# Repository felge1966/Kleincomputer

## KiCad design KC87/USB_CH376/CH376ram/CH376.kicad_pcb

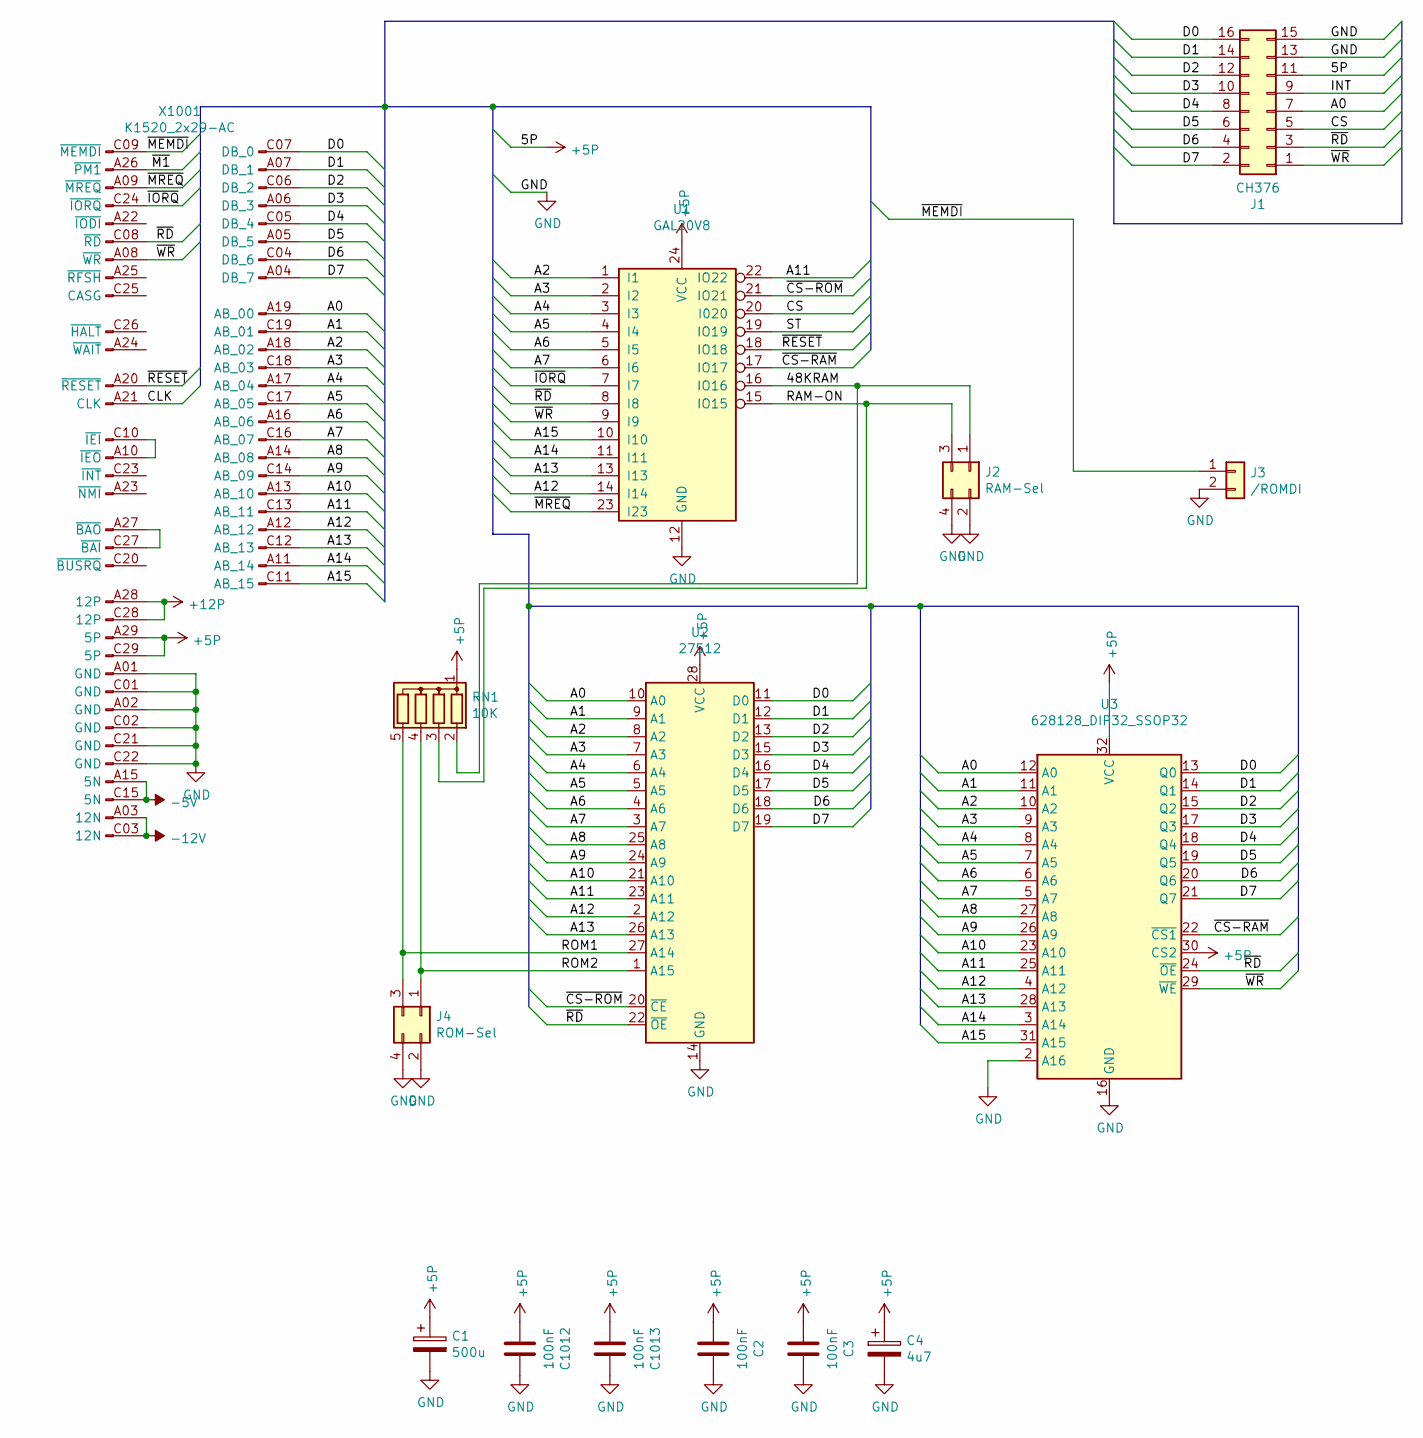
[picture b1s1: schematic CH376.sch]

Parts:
C1: 500u; CP_Radial_D8.0mm_P2.50mm
C2, C3, C1012, C1013: 100nF; C_Disc_D3.0mm_W2.0mm_P2.50mm
C4: 4u7; CP_Radial_D5.0mm_P2.50mm
J1: CH376; PinSocket_2x08_P2.54mm_Vertical
J2: RAM-Sel; PinHeader_2x02_P2.54mm_Horizontal
J3: /ROMDI; PinHeader_1x02_P2.54mm_Horizontal
J4: ROM-Sel; PinHeader_2x02_P2.54mm_Horizontal
RN1: 10K; R_Array_SIP5
U1: GAL20V8; DIP-24_W7.62mm_LongPads
U2: 27512; DIP-28_W15.24mm
U3: 628128_DIP32_SSOP32; DIP-32_W15.24mm_LongPads
X1001: K1520_2x29-AC; K1520_EFS2x29_DIN_male

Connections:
+5P: C1.1, C2.2, C3.2, C4.1, C1012.2, C1013.2, J1.11, RN1.1 (common), U1.24 (VCC), U2.28 (VCC), U3.30 (CS2), U3.32 (VCC), X1001.A29 (5P), X1001.C29 (5P)
+12P: X1001.A28 (12P), X1001.C28 (12P)
-5V: X1001.A15 (5N), X1001.C15 (5N)
-12V: X1001.A03 (12N), X1001.C03 (12N)
/48KRAM: J2.1, RN1.2 (R1), U1.16 (IO16)
/A0: J1.7, U2.10 (A0), U3.12 (A0), X1001.A19 (AB_00)
/A1: U2.9 (A1), U3.11 (A1), X1001.C19 (AB_01)
/A2: U1.1 (I1), U2.8 (A2), U3.10 (A2), X1001.A18 (AB_02)
/A3: U1.2 (I2), U2.7 (A3), U3.9 (A3), X1001.C18 (AB_03)
/A4: U1.3 (I3), U2.6 (A4), U3.8 (A4), X1001.A17 (AB_04)
/A5: U1.4 (I4), U2.5 (A5), U3.7 (A5), X1001.C17 (AB_05)
/A6: U1.5 (I5), U2.4 (A6), U3.6 (A6), X1001.A16 (AB_06)
/A7: U1.6 (I6), U2.3 (A7), U3.5 (A7), X1001.C16 (AB_07)
/A8: U2.25 (A8), U3.27 (A8), X1001.A14 (AB_08)
/A9: U2.24 (A9), U3.26 (A9), X1001.C14 (AB_09)
/A10: U2.21 (A10), U3.23 (A10), X1001.A13 (AB_10)
/A11: U1.22 (IO22), U2.23 (A11), U3.25 (A11), X1001.C13 (AB_11)
/A12: U1.14 (I14), U2.2 (A12), U3.4 (A12), X1001.A12 (AB_12)
/A13: U1.13 (I13), U2.26 (A13), U3.28 (A13), X1001.C12 (AB_13)
/A14: U1.11 (I11), U3.3 (A14), X1001.A11 (AB_14)
/A15: U1.10 (I10), U3.31 (A15), X1001.C11 (AB_15)
/CLK: X1001.A21 (CLK)
/CS: J1.5, U1.20 (I020)
/D0: J1.16, U2.11 (D0), U3.13 (Q0), X1001.C07 (DB_0)
/D1: J1.14, U2.12 (D1), U3.14 (Q1), X1001.A07 (DB_1)
/D2: J1.12, U2.13 (D2), U3.15 (Q2), X1001.C06 (DB_2)
/D3: J1.10, U2.15 (D3), U3.17 (Q3), X1001.A06 (DB_3)
/D4: J1.8, U2.16 (D4), U3.18 (Q4), X1001.C05 (DB_4)
/D5: J1.6, U2.17 (D5), U3.19 (Q5), X1001.A05 (DB_5)
/D6: J1.4, U2.18 (D6), U3.20 (Q6), X1001.C04 (DB_6)
/D7: J1.2, U2.19 (D7), U3.21 (Q7), X1001.A04 (DB_7)
/RAM-ON: J2.3, RN1.3 (R2), U1.15 (IO15)
/ROM1: J4.3, RN1.5 (R4), U2.27 (A14)
/ROM2: J4.1, RN1.4 (R3), U2.1 (A15)
/~CS-RAM: U1.17 (IO17), U3.22 (~CS1)
/~CS-ROM: U1.21 (IO21), U2.20 (~CE)
/~IORQ: U1.7 (I7), X1001.C24 (~IORQ)
/~M1: X1001.A26 (~PM1)
/~MEMDI: J3.1, X1001.C09 (~MEMDI)
/~MREQ: U1.23 (I23), X1001.A09 (~MREQ)
/~RD: J1.3, U1.8 (I8), U2.22 (~OE), U3.24 (~OE), X1001.C08 (~RD)
/~RESET: U1.18 (IO18), X1001.A20 (~RESET)
/~WR: J1.1, U1.9 (I9), U3.29 (~WE), X1001.A08 (~WR)
GND: C1.2, C2.1, C3.1, C4.2, C1012.1, C1013.1, J1.13, J1.15, J2.2, J2.4, J3.2, J4.2, J4.4, U1.12 (GND), U2.14 (GND), U3.2 (A16), U3.16 (GND), X1001.A01 (GND), X1001.A02 (GND), X1001.C01 (GND), X1001.C02 (GND), X1001.C21 (GND), X1001.C22 (GND)
unnamed: X1001.A10 (~IEO), X1001.C10 (~IEI)
unnamed: X1001.A27 (~BAO), X1001.C27 (~BAI)

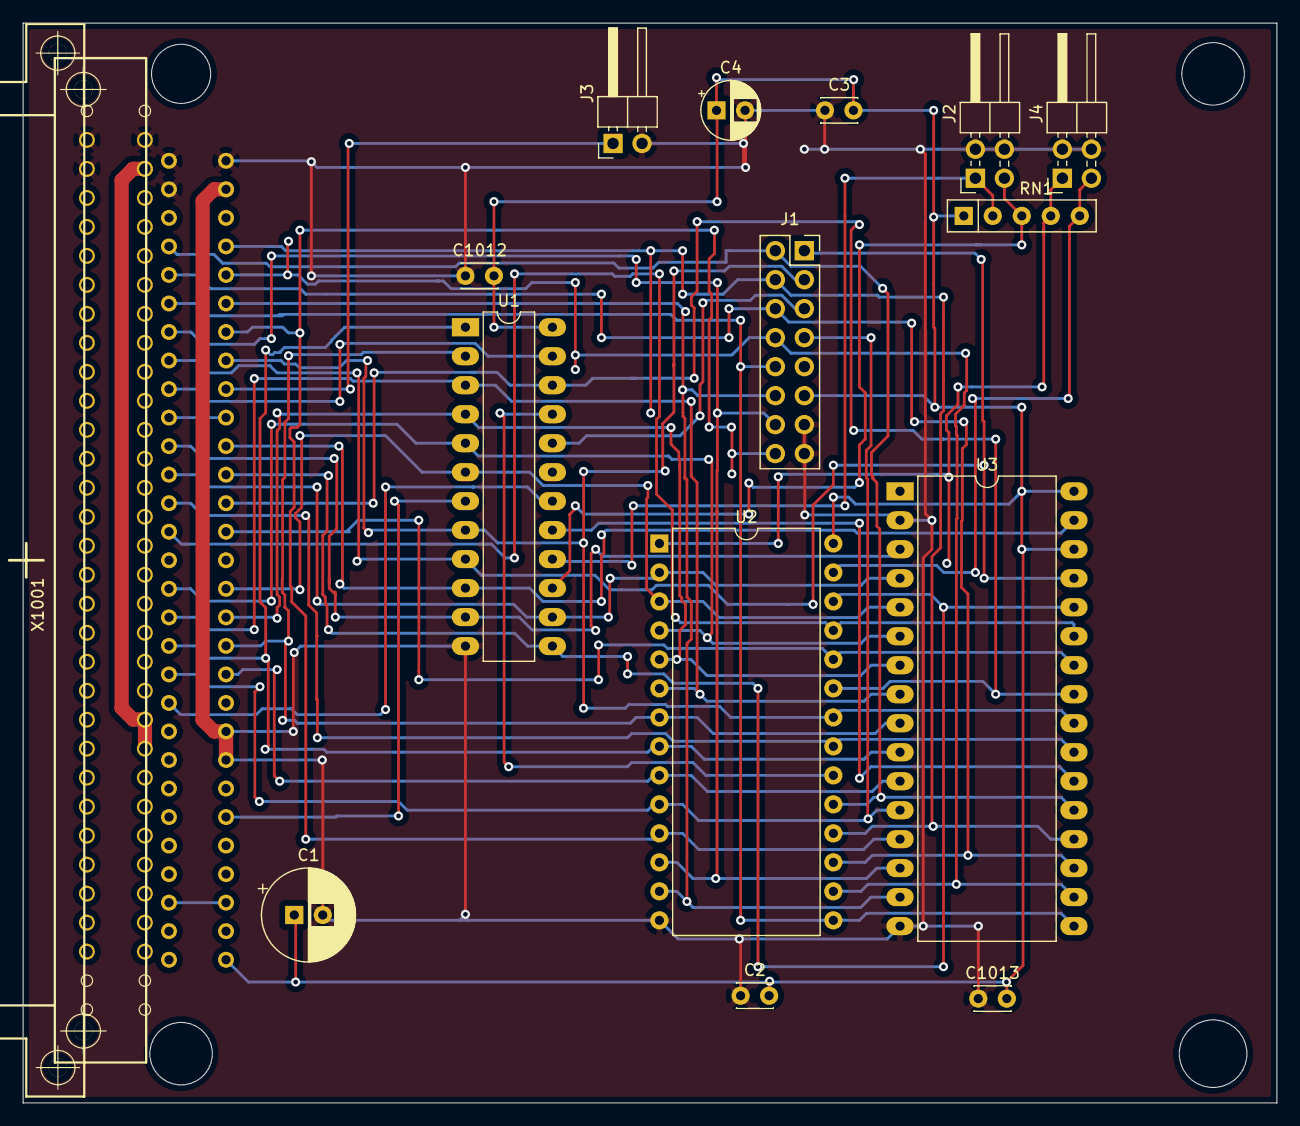
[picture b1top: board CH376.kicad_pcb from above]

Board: 2 copper layers, 109.9 x 94.6 mm, 15 parts (0 on the bottom side), 44 nets.

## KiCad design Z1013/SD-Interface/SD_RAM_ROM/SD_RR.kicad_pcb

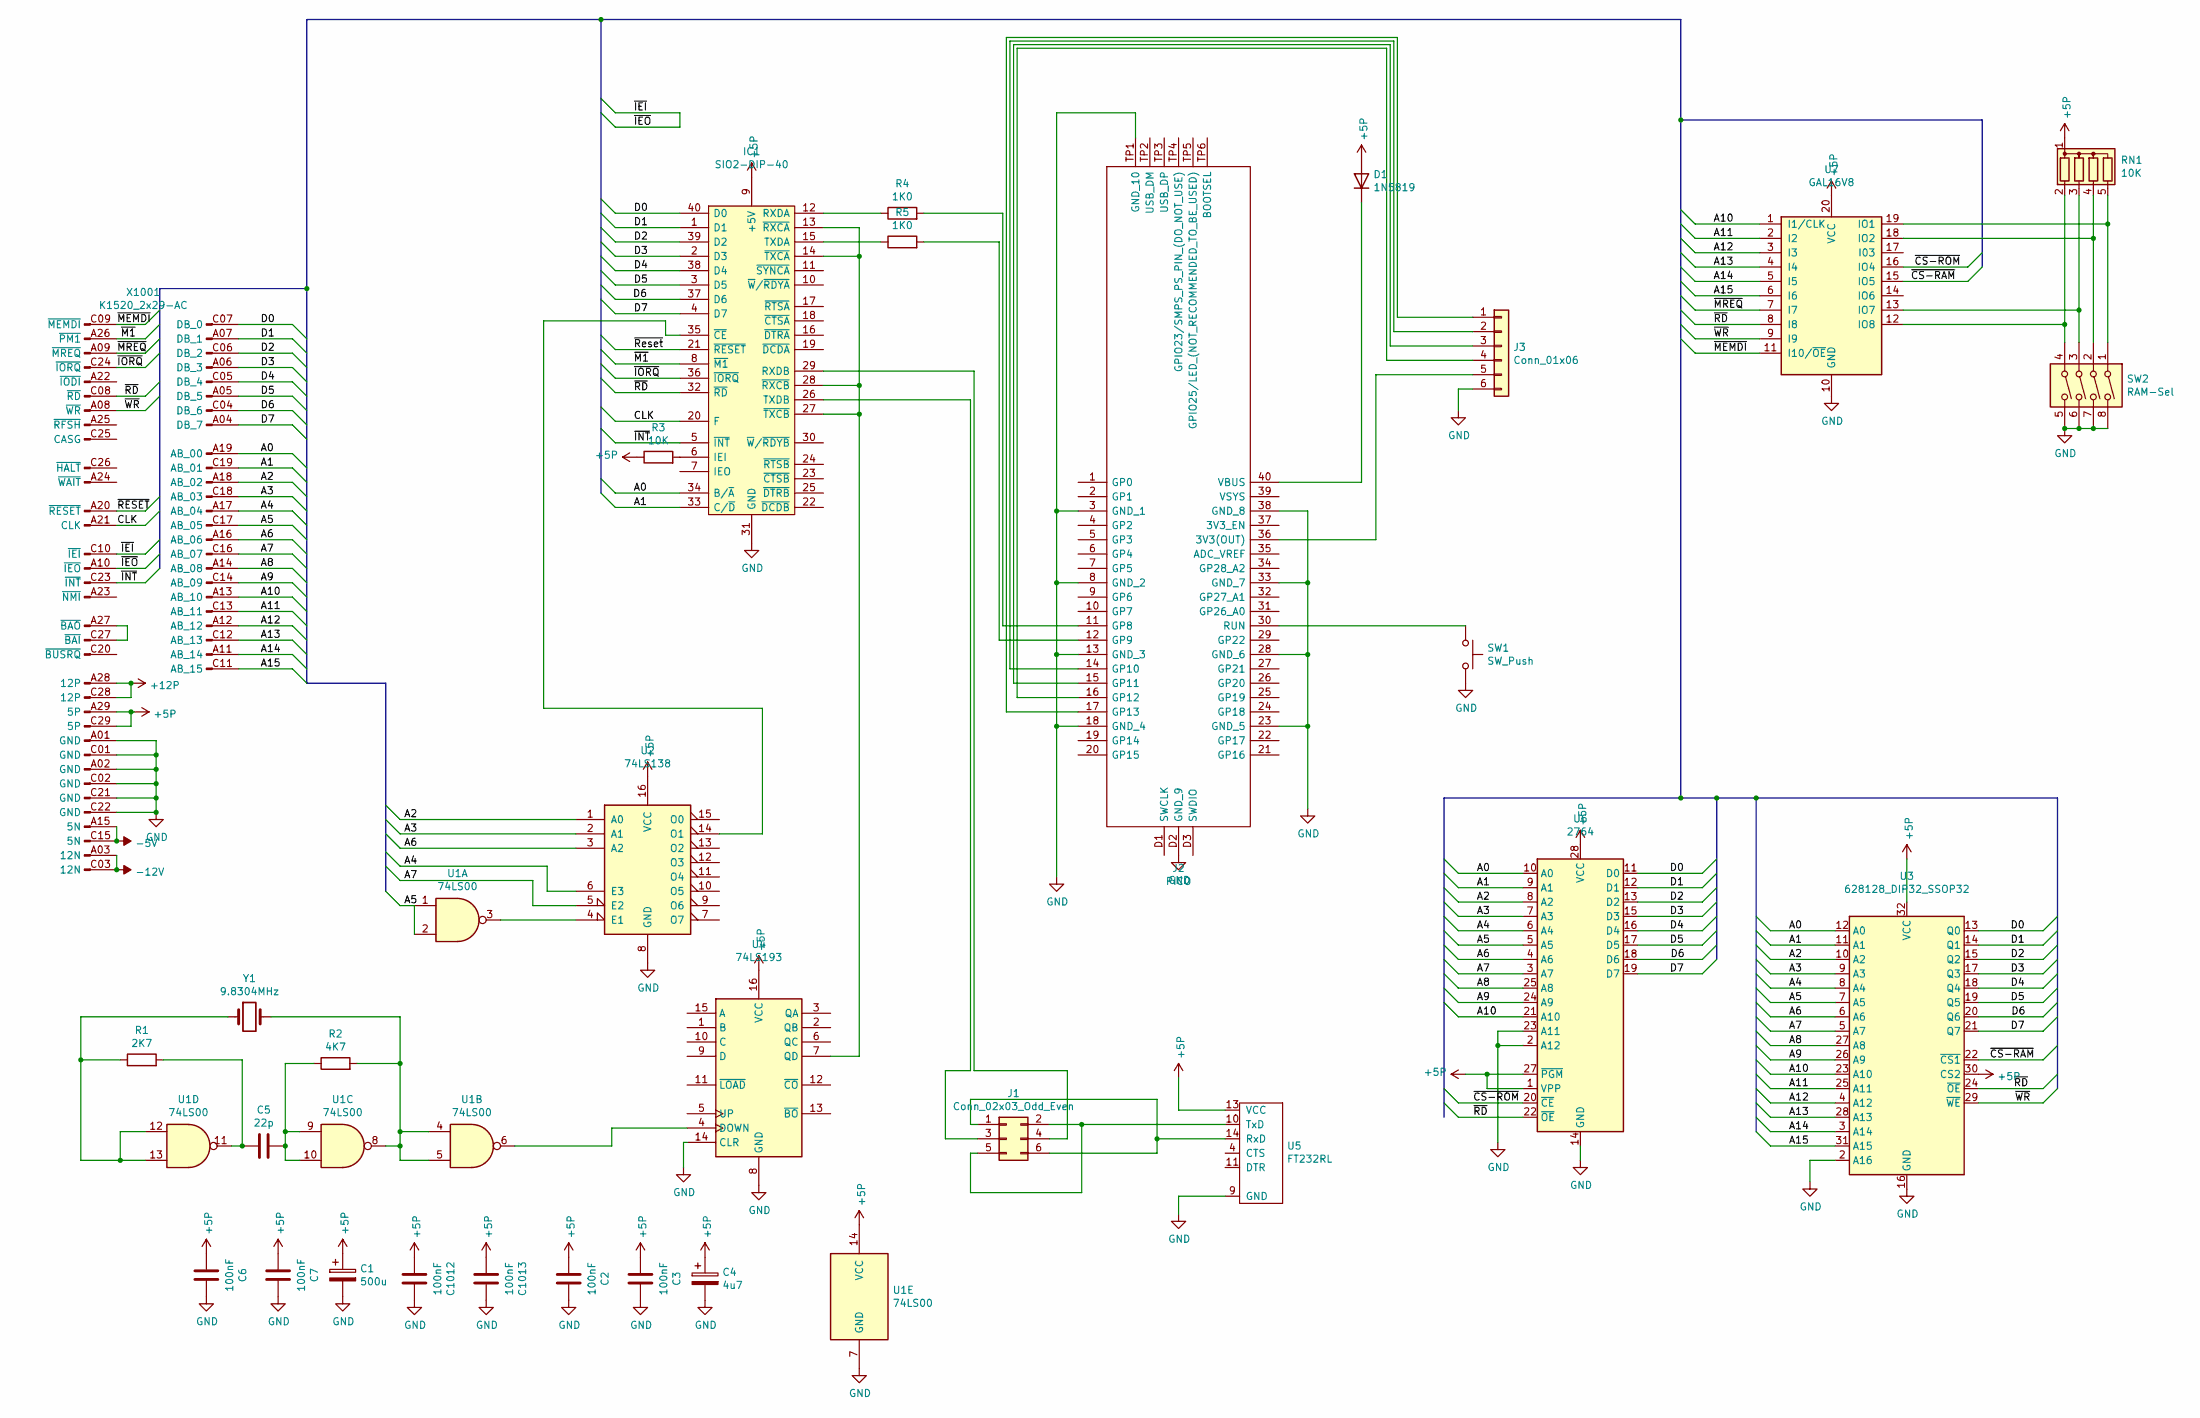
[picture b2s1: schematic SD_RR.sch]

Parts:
C1: 500u; CP_Radial_D8.0mm_P3.80mm
C2, C3, C6, C7, C1012, C1013: 100nF; C_Disc_D3.0mm_W2.0mm_P2.50mm
C4: 4u7; CP_Radial_D5.0mm_P2.50mm
C5: 22p; C_Disc_D3.0mm_W2.0mm_P2.50mm
D1: 1N5819; D_DO-15_P10.16mm_Horizontal
IC1: SIO2-DIP-40; DIP-40_W15.24mm_LongPads; Manufacturer_Part_Number Z84C4206PEG; Mouser Part Number 692-Z84C4206PEG
J1: Conn_02x03_Odd_Even; PinHeader_2x03_P2.54mm_Vertical
J2: PICO; Manufacturer_Part_Number PICO
J3: Conn_01x06; PinSocket_1x06_P2.54mm_Vertical
R1: 2K7; R_Axial_DIN0207_L6.3mm_D2.5mm_P10.16mm_Horizontal
R2: 4K7; R_Axial_DIN0207_L6.3mm_D2.5mm_P10.16mm_Horizontal
R3: 10K; R_Axial_DIN0207_L6.3mm_D2.5mm_P10.16mm_Horizontal
R4, R5: 1K0; R_Axial_DIN0207_L6.3mm_D2.5mm_P10.16mm_Horizontal
RN1: 10K; R_Array_SIP5
SW1: SW_Push; SW_Tactile_SKHH_Angled
SW2: RAM-Sel; SW_DIP_SPSTx04_Slide_6.7x11.72mm_W7.62mm_P2.54mm_LowProfile
U1: 74LS00; DIP-14_W7.62mm_LongPads
U2: 74LS138; DIP-16_W7.62mm_LongPads
U3: 628128_DIP32_SSOP32; DIP-32_W15.24mm_LongPads
U4: 74LS193; DIP-16_W7.62mm_LongPads
U5: FT232RL; FT232R
U6: 2764; DIP-28_W15.24mm_LongPads
U7: GAL16V8; DIP-20_W7.62mm_LongPads
X1001: K1520_2x29-AC; K1520_EFS2x29_DIN_male
Y1: 9.8304MHz; Crystal_HC49-U_Horizontal

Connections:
+5P: C1.1, C2.2, C3.2, C4.1, C6.2, C7.2, C1012.2, C1013.2, D1.2 (A), IC1.9 (+5V), R3.1, RN1.1 (common), U1.14 (VCC), U2.16 (VCC), U3.30 (CS2), U3.32 (VCC), U4.16 (VCC), U5.13 (VCC), U6.1 (VPP), U6.27 (~PGM), U6.28 (VCC), U7.20 (VCC), X1001.A29 (5P), X1001.C29 (5P)
+12P: X1001.A28 (12P), X1001.C28 (12P)
-5V: X1001.A15 (5N), X1001.C15 (5N)
-12V: X1001.A03 (12N), X1001.C03 (12N)
/A0: IC1.34 (B/~A), U3.12 (A0), U6.10 (A0), X1001.A19 (AB_00)
/A1: IC1.33 (C/~D), U3.11 (A1), U6.9 (A1), X1001.C19 (AB_01)
/A2: U2.1 (A0), U3.10 (A2), U6.8 (A2), X1001.A18 (AB_02)
/A3: U2.2 (A1), U3.9 (A3), U6.7 (A3), X1001.C18 (AB_03)
/A4: U2.6 (E3), U3.8 (A4), U6.6 (A4), X1001.A17 (AB_04)
/A5: U1.1, U1.2, U3.7 (A5), U6.5 (A5), X1001.C17 (AB_05)
/A6: U2.3 (A2), U3.6 (A6), U6.4 (A6), X1001.A16 (AB_06)
/A7: U2.5 (E2), U3.5 (A7), U6.3 (A7), X1001.C16 (AB_07)
/A8: U3.27 (A8), U6.25 (A8), X1001.A14 (AB_08)
/A9: U3.26 (A9), U6.24 (A9), X1001.C14 (AB_09)
/A10: U3.23 (A10), U6.21 (A10), U7.1 (I1/CLK), X1001.A13 (AB_10)
/A11: U3.25 (A11), U7.2 (I2), X1001.C13 (AB_11)
/A12: U3.4 (A12), U7.3 (I3), X1001.A12 (AB_12)
/A13: U3.28 (A13), U7.4 (I4), X1001.C12 (AB_13)
/A14: U3.3 (A14), U7.5 (I5), X1001.A11 (AB_14)
/A15: U3.31 (A15), U7.6 (I6), X1001.C11 (AB_15)
/CLK: IC1.20 (F), X1001.A21 (CLK)
/D0: IC1.40 (D0), U3.13 (Q0), U6.11 (D0), X1001.C07 (DB_0)
/D1: IC1.1 (D1), U3.14 (Q1), U6.12 (D1), X1001.A07 (DB_1)
/D2: IC1.39 (D2), U3.15 (Q2), U6.13 (D2), X1001.C06 (DB_2)
/D3: IC1.2 (D3), U3.17 (Q3), U6.15 (D3), X1001.A06 (DB_3)
/D4: IC1.38 (D4), U3.18 (Q4), U6.16 (D4), X1001.C05 (DB_4)
/D5: IC1.3 (D5), U3.19 (Q5), U6.17 (D5), X1001.A05 (DB_5)
/D6: IC1.37 (D6), U3.20 (Q6), U6.18 (D6), X1001.C04 (DB_6)
/D7: IC1.4 (D7), U3.21 (Q7), U6.19 (D7), X1001.A04 (DB_7)
/~CS-RAM: U3.22 (~CS1), U7.15 (IO5)
/~CS-ROM: U6.20 (~CE), U7.16 (IO4)
/~IEI: X1001.A10 (~IEO), X1001.C10 (~IEI)
/~INT: IC1.5 (~INT), X1001.C23 (~INT)
/~IORQ: IC1.36 (~IORQ), X1001.C24 (~IORQ)
/~M1: IC1.8 (~M1), X1001.A26 (~PM1)
/~MEMDI: U7.11 (I10/~OE~), X1001.C09 (~MEMDI)
/~MREQ: U7.7 (I7), X1001.A09 (~MREQ)
/~RD: IC1.32 (~RD), U3.24 (~OE), U6.22 (~OE), U7.8 (I8), X1001.C08 (~RD)
/~RESET: X1001.A20 (~RESET)
/~WR: U3.29 (~WE), U7.9 (I9), X1001.A08 (~WR)
GND: C1.2, C2.1, C3.1, C4.2, C6.1, C7.1, C1012.1, C1013.1, IC1.31 (GND), J2.3 (GND_1), J2.8 (GND_2), J2.13 (GND_3), J2.18 (GND_4), J2.23 (GND_5), J2.28 (GND_6), J2.33 (GND_7), J2.38 (GND_8), J2.D2 (GND_9), J2.TP1 (GND_10), J3.6, SW1.2, SW2.5, SW2.6, SW2.7, SW2.8, U1.7 (GND), U2.8 (GND), U3.2 (A16), U3.16 (GND), U4.8 (GND), U4.14 (CLR), U5.9 (GND), U6.2 (A12), U6.14 (GND), U6.23 (A11), U7.10 (GND), X1001.A01 (GND), X1001.A02 (GND), X1001.C01 (GND), X1001.C02 (GND), X1001.C21 (GND), X1001.C22 (GND)
unnamed: C5.1, R1.2, U1.11
unnamed: C5.2, R2.1, U1.9, U1.10
unnamed: D1.1 (K), J2.40 (VBUS)
unnamed: IC1.6 (IEI), R3.2
unnamed: IC1.12 (RXDA), R4.1
unnamed: IC1.13 (~RXCA), IC1.14 (~TXCA), IC1.27 (~TXCB), IC1.28 (~RXCB), U4.7 (QD)
unnamed: IC1.15 (TXDA), R5.1
unnamed: IC1.26 (TXDB), J1.3
unnamed: IC1.29 (RXDB), J1.4
unnamed: IC1.35 (~CE), U2.14 (O1)
unnamed: J1.1, J1.6, U5.14 (RxD)
unnamed: J1.2, J1.5, U5.10 (TxD)
unnamed: J2.11 (GP8), R4.2
unnamed: J2.12 (GP9), R5.2
unnamed: J2.14 (GP10), J3.2
unnamed: J2.15 (GP11), J3.3
unnamed: J2.16 (GP12), J3.4
unnamed: J2.17 (GP13), J3.1
unnamed: J2.30 (RUN), SW1.1
unnamed: J2.36 (3V3(OUT)), J3.5
unnamed: R1.1, U1.12, U1.13, Y1.1
unnamed: R2.2, U1.4, U1.5, U1.8, Y1.2
unnamed: RN1.2 (R1), SW2.4, U7.12 (IO8)
unnamed: RN1.3 (R2), SW2.3, U7.13 (IO7)
unnamed: RN1.4 (R3), SW2.2, U7.18 (IO2)
unnamed: RN1.5 (R4), SW2.1, U7.19 (IO1)
unnamed: U1.3, U2.4 (E1)
unnamed: U1.6, U4.4 (DOWN)
unnamed: X1001.A27 (~BAO), X1001.C27 (~BAI)

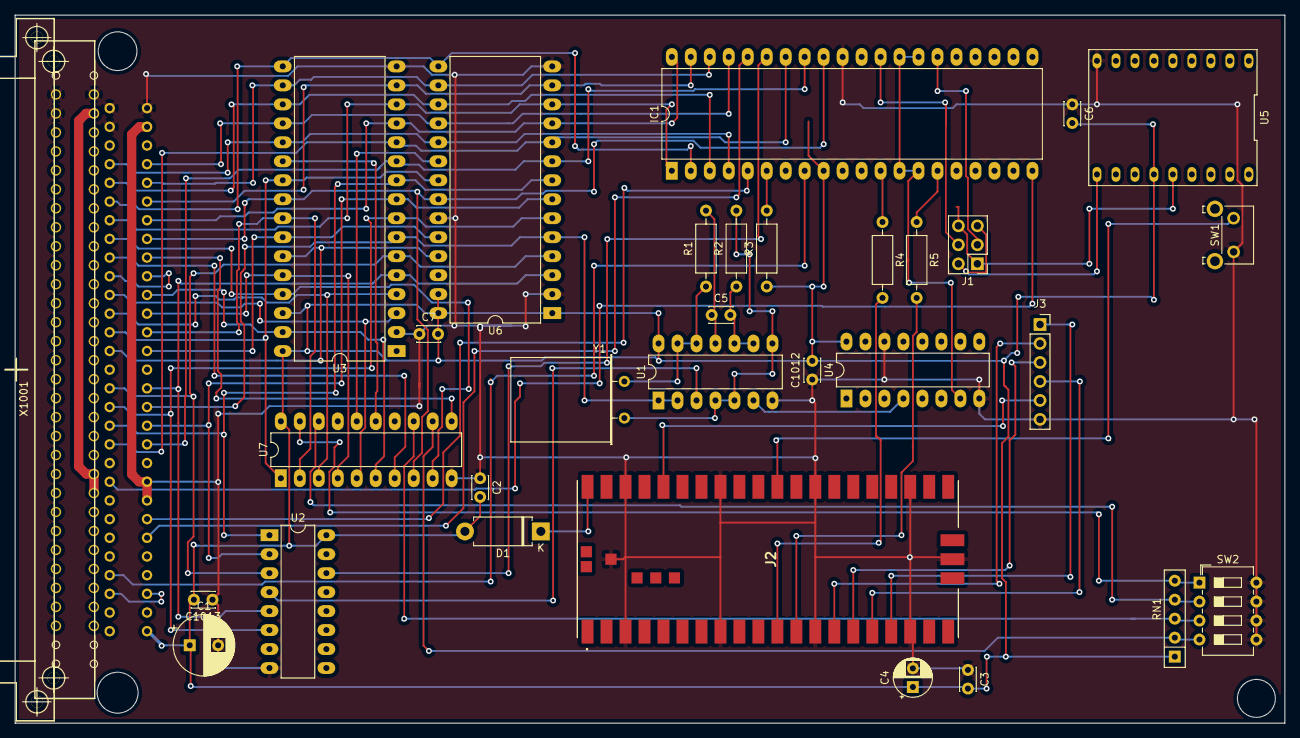
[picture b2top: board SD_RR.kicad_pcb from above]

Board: 2 copper layers, 169.9 x 94.7 mm, 31 parts (0 on the bottom side), 69 nets.
